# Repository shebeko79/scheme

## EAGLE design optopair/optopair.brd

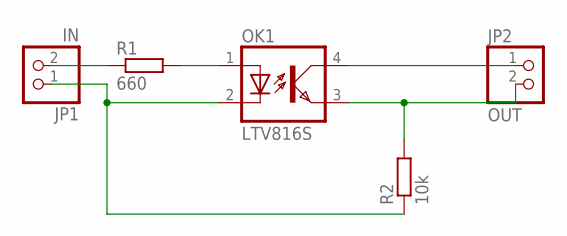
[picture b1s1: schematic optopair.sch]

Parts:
JP1: IN; 1X02
JP2: OUT; 1X02
OK1: LTV816S; SMD4
R1: 660; R0805
R2: 10k; R0805

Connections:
unnamed: JP1.2, R1.1
unnamed: OK1.1 (A), R1.2
unnamed: JP1.1, OK1.2 (C), R2.1
unnamed: JP2.2, OK1.3 (EMIT), R2.2
unnamed: JP2.1, OK1.4 (COL)

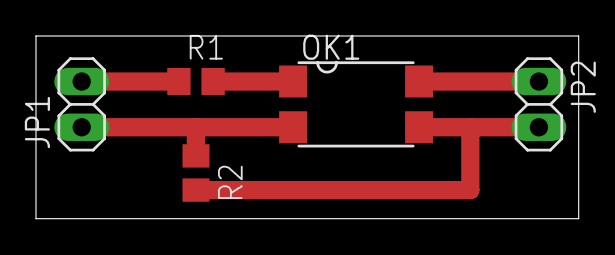
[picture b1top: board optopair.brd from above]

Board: 2 copper layers, 30.2 x 10.2 mm, 5 parts (0 on the bottom side), 5 nets.

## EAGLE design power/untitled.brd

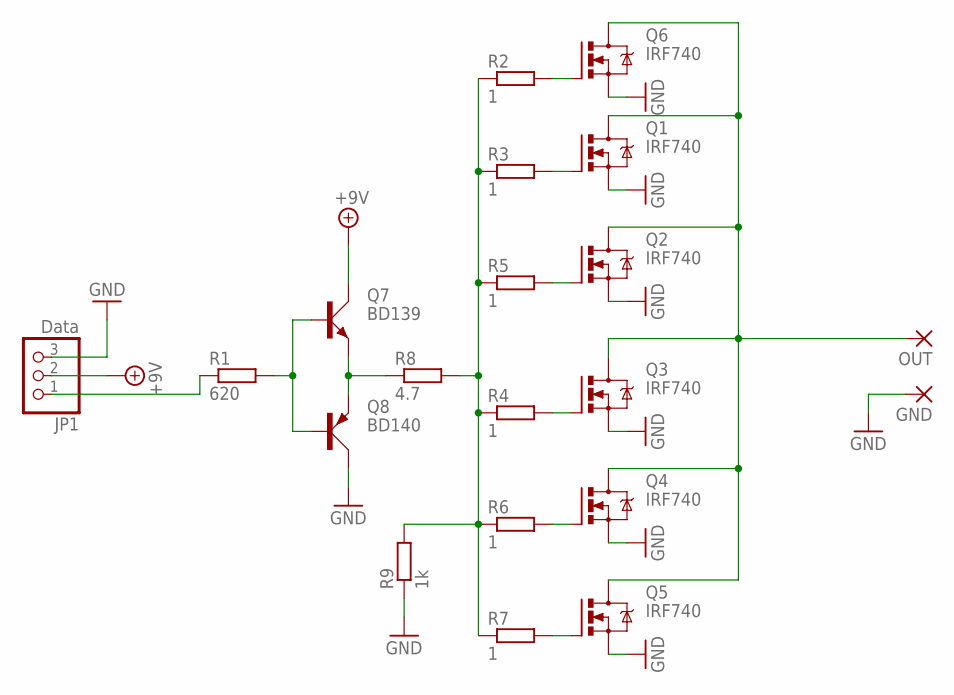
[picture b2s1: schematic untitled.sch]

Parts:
GND: WIREPADSMD5-2,5; 5-2,5
JP1: Data; 1X03
OUT: WIREPADSMD5-2,5; 5-2,5
Q1, Q2, Q3, Q4, Q5, Q6: IRF740; TO220BV
Q7: BD139; TO126AV
Q8: BD140; TO126AV
R1: 620; R0805
R2, R3, R4, R5, R6, R7: 1; R0805
R8: 4.7; R0805
R9: 1k; R0805

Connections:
+9V: JP1.2, Q7.C
GND: GND.1, JP1.3, Q1.S, Q2.S, Q3.S, Q4.S, Q5.S, Q6.S, Q8.C, R9.1
unnamed: Q7.B, Q8.B, R1.2
unnamed: OUT.1, Q1.D, Q2.D, Q3.D, Q4.D, Q5.D, Q6.D
unnamed: Q7.E, Q8.E, R8.1
unnamed: R2.1, R3.1, R4.1, R5.1, R6.1, R7.1, R8.2, R9.2
unnamed: Q6.G, R2.2
unnamed: Q1.G, R3.2
unnamed: Q2.G, R5.2
unnamed: Q3.G, R4.2
unnamed: Q4.G, R6.2
unnamed: Q5.G, R7.2
unnamed: JP1.1, R1.1

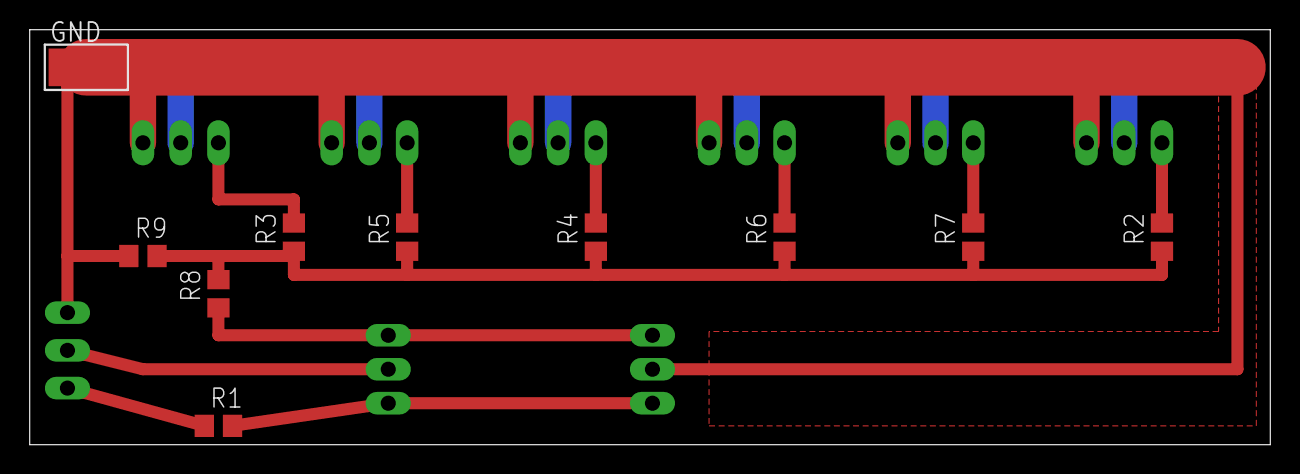
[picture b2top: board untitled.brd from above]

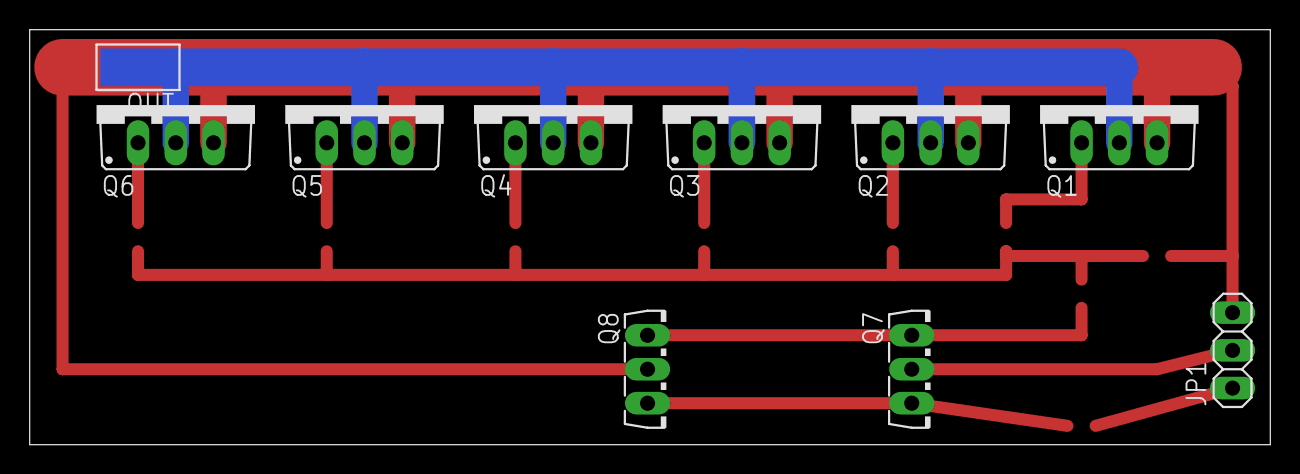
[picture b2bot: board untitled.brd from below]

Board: 2 copper layers, 83.5 x 27.9 mm, 20 parts (10 on the bottom side), 13 nets.

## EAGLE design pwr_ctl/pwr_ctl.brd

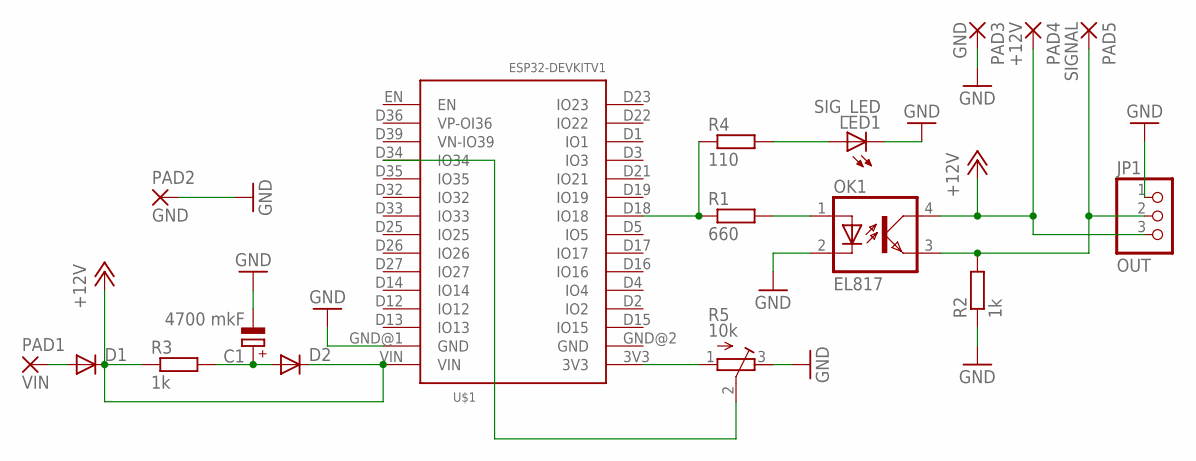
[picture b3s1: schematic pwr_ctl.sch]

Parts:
C1: 4700 mkF; E7,5-18
D1, D2: CGRM4007-G; SOD-123_MINI-SMA
JP1: OUT; 1X03
LED1: SIG_LED; SML0805
OK1: EL817; SMD4
PAD1: VIN; SMD2,54-5,08
PAD2, PAD3: GND; SMD2,54-5,08
PAD4: +12V; SMD2,54-5,08
PAD5: SIGNAL; SMD2,54-5,08
R1: 660; R0805
R2, R3: 1k; R0805
R4: 110; R0805
R5: 10k; RTRIM3296W
U$1: ESP32DEVKITV1; ESP32-DEVKITV1

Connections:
+12V: D1.C, D2.C, JP1.3, OK1.4 (COL), PAD4.1, R3.1, U$1.VIN
GND: C1.-, JP1.1, LED1.C, OK1.2 (C), PAD2.1, PAD3.1, R2.1, R5.3 (E), U$1.GND@1 (GND)
unnamed: R1.1, R4.1, U$1.D18 (IO18)
unnamed: OK1.1 (A), R1.2
unnamed: R5.1 (A), U$1.3V3
unnamed: C1.+, D2.A, R3.2
unnamed: LED1.A, R4.2
unnamed: D1.A, PAD1.1
unnamed: JP1.2, OK1.3 (EMIT), PAD5.1, R2.2
unnamed: R5.2 (S), U$1.D34 (IO34)

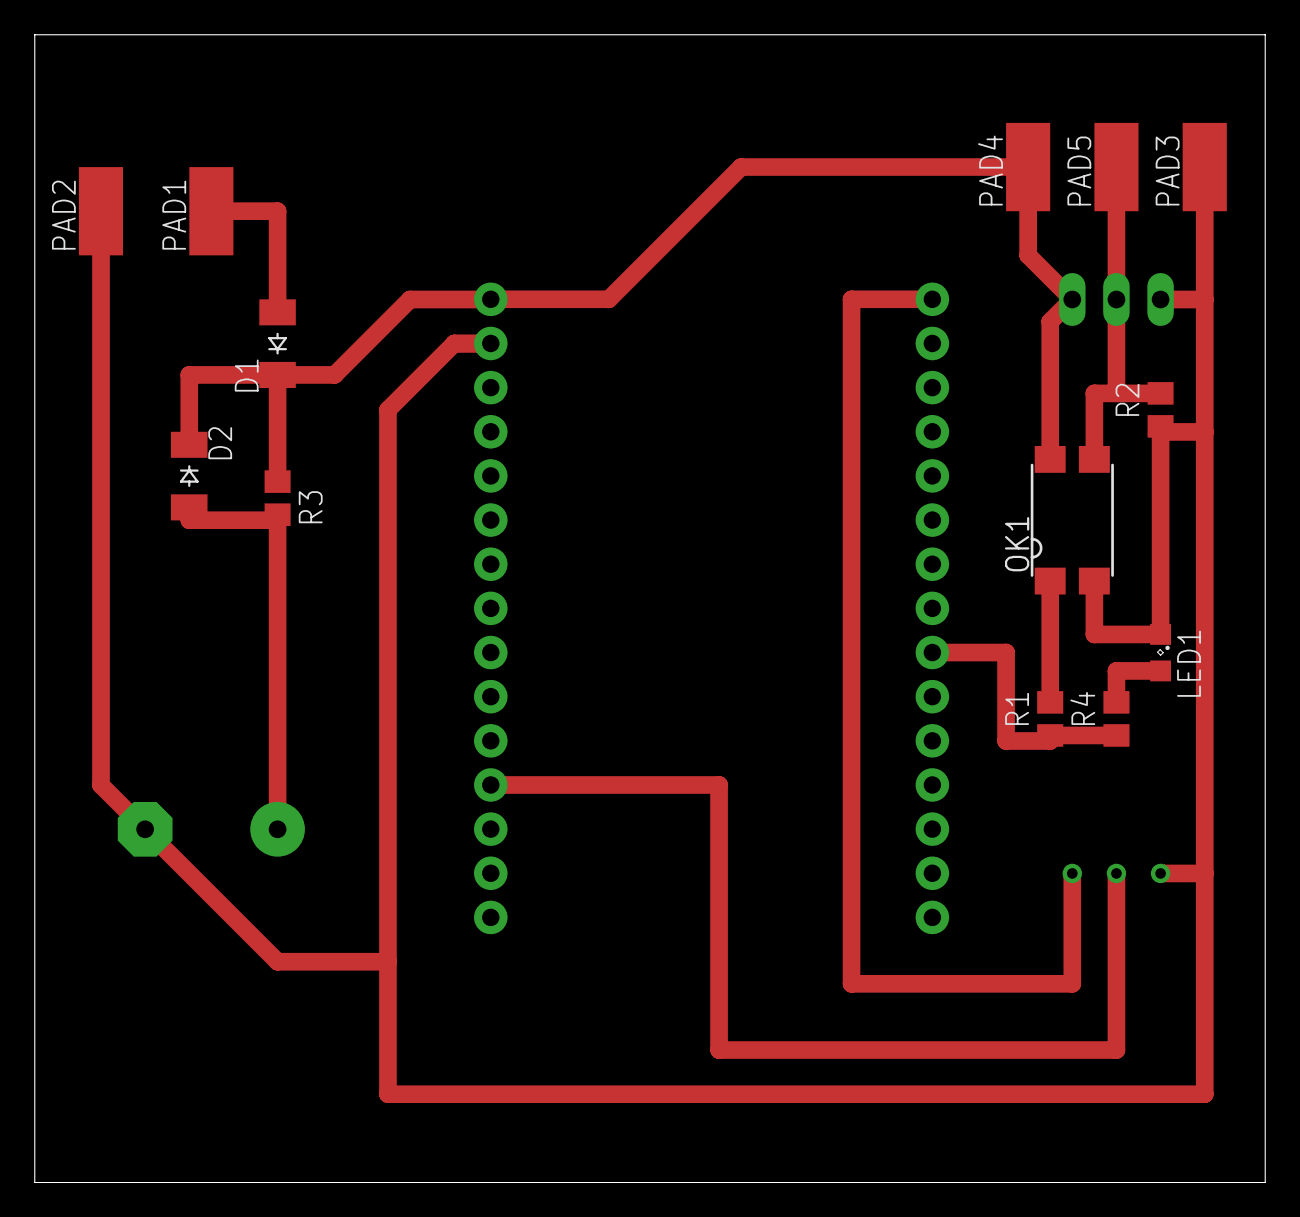
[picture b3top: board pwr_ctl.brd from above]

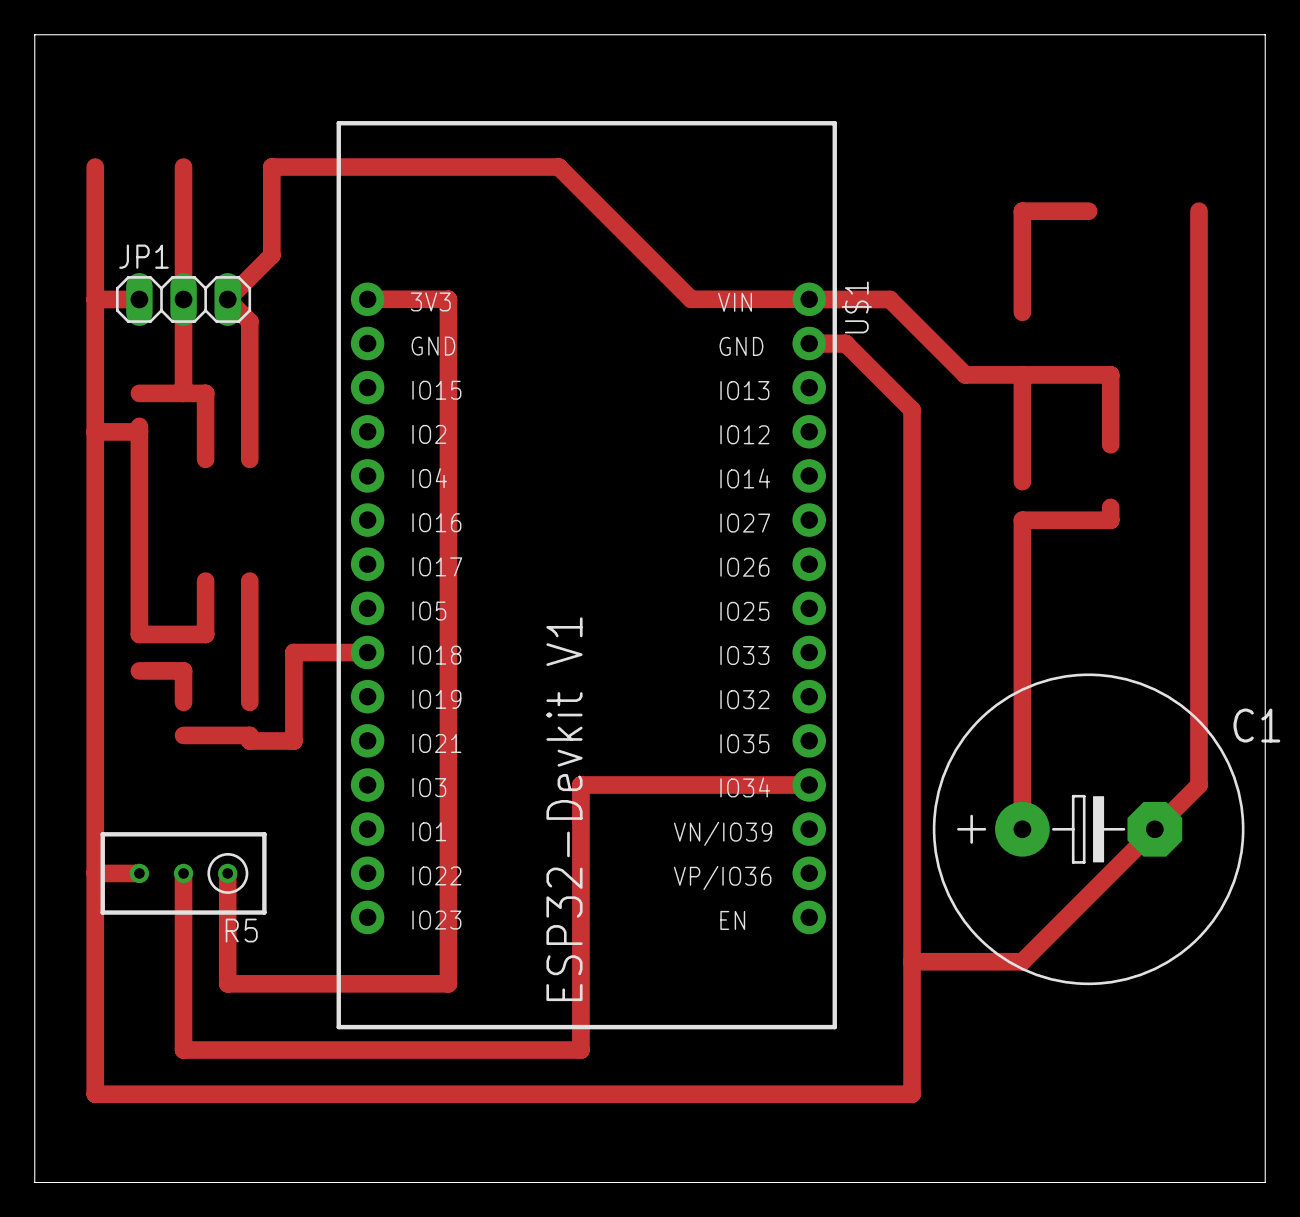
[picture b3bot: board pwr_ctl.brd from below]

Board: 2 copper layers, 70.8 x 66.0 mm, 17 parts (4 on the bottom side), 10 nets.

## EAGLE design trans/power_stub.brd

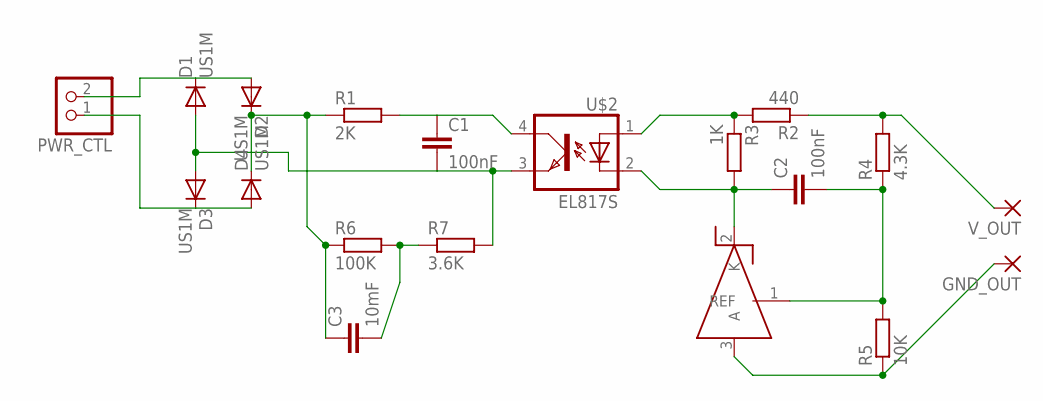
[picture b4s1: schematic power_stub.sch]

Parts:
C1, C2: 100nF; C0805
C3: 10mF; C0805
D1, D2, D3, D4: US1M; DO-214AC
GND_OUT: SMD5; SMD2,54-5,08
PWR_CTL: PINHD-1X2/90; 1X02/90
R1: 2K; R0805
R2: 440; R0805
R3: 1K; R0805
R4: 4.3K; R0805
R5: 10K; R0805
R6: 100K; R0805
R7: 3.6K; R0805
U$1: TL431AIDBZR; SOT23
U$2: EL817S; SMD4_L
V_OUT: SMD5; SMD2,54-5,08

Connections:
GND: GND_OUT.1, R5.1, U$1.3 (A)
GND_HI: C1.2, D1.A, D3.A, R7.2, U$2.3 (EMIT)
unnamed: D1.C, D2.A, PWR_CTL.2
unnamed: C1.1, R1.2, U$2.4 (COL)
unnamed: D3.C, D4.A, PWR_CTL.1
unnamed: C2.1, R3.2, U$1.2 (K), U$2.2 (C)
unnamed: R2.1, R4.2, V_OUT.1
unnamed: C2.2, R4.1, R5.2, U$1.1 (REF)
unnamed: C3.2, R6.2, R7.1
unnamed: R2.2, R3.1, U$2.1 (A)
V_HI: C3.1, D2.C, D4.C, R1.1, R6.1

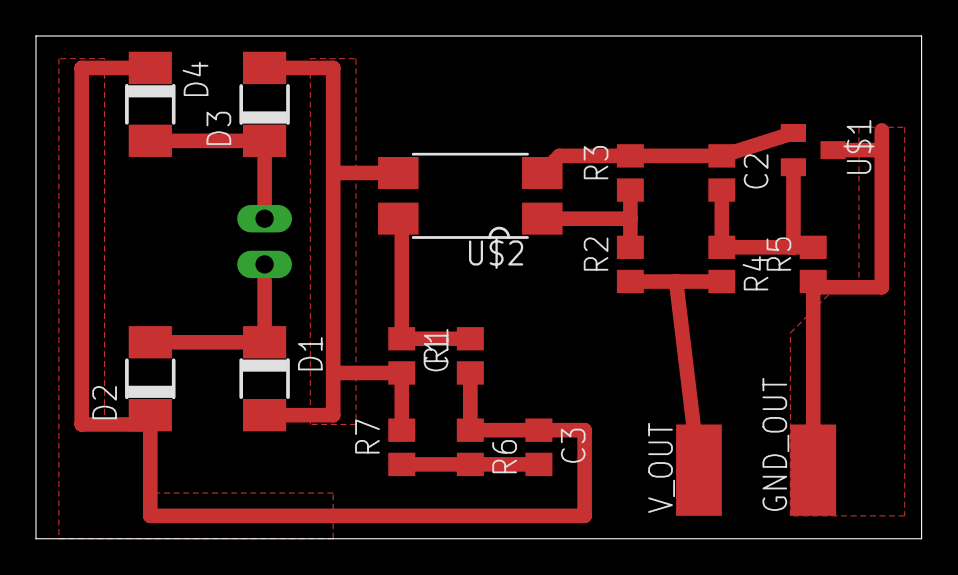
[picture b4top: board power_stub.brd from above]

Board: 2 copper layers, 49.2 x 27.9 mm, 19 parts (1 on the bottom side), 11 nets.

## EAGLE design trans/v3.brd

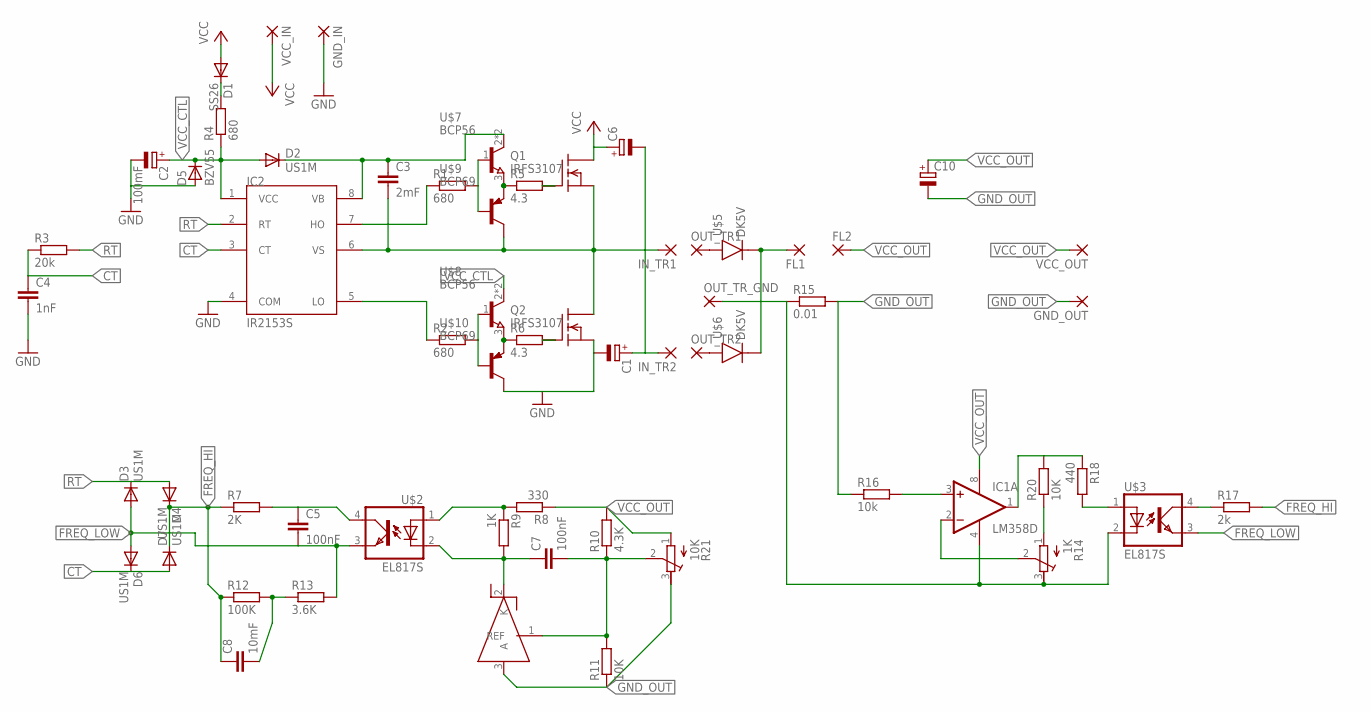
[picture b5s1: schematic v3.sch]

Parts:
C1, C6: CPOL-EUE10-22.5; EB22,5D
C2: 100mF; E5-10,5
C3: 2mF; C0805
C4: 1nF; C0805
C5, C7: 100nF; C0805
C8: 10mF; C0805
C10: CPOL-EUE7.5-18; E7,5-18
D1: SS26; DO-214AC
D2, D3, D4, D6, D7: US1M; DO-214AC
D5: BZV55; SOD80
FL1, FL2: 3,81/1,4
GND_IN: 3,81/1,4
GND_OUT: 3,81/1,4
IC1: LM358D; SO08
IC2: IR2153S; SO08
IN_TR1, IN_TR2: 3,81/1,4
OUT_TR1, OUT_TR2: 3,81/1,4
OUT_TR_GND: 3,81/1,4
Q1, Q2: IRFS3107; D2PAK
R1, R2, R4: 680; R0805
R3: 20k; R0805
R5, R6: 4.3; R0805
R7: 2K; R0805
R8: 330; R0805
R9: 1K; R0805
R10: 4.3K; R0805
R11: 10K; R0805
R12: 100K; R0805
R13: 3.6K; R0805
R14: 1K; RTRIM3296W
R15: 0.01; R2512
R16: 10k; M0805
R17: 2k; M0805
R18: 440; M0805
R20: 10K; M0805
R21: 10K; RTRIM3296W
U$1: TL431; SOT23
U$2, U$3: EL817S; SMD4_L
U$5, U$6: DK5V; TO220(V)
U$7, U$8: BCP56; SOT223
U$9, U$10: BCP69; SOT223
VCC_IN: 3,81/1,4
VCC_OUT: 3,81/1,4

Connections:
CT: C4.1, D6.C, D7.A, IC2.3 (CT), R3.1
FREQ_HI: C8.1, D4.C, D7.C, R7.1, R12.1, R17.2
FREQ_LOW: C5.2, D3.A, D6.A, R13.2, U$2.3 (EMIT), U$3.3 (EMIT)
GND: C1.-, C2.-, C4.2, D5.2 (A), GND_IN.1, IC2.4 (COM), Q2.3 (S), U$10.2 (C), U$10.4 (C)
GND_OUT: C10.-, GND_OUT.1, R11.1, R15.2, R16.1, R21.3 (E), U$1.3 (A)
IN_TR1: C3.2, IC2.6 (VS), IN_TR1.1, Q1.3 (S), Q2.2 (D), U$9.2 (C), U$9.4 (C)
IN_TR2: C1.+, C6.-, IN_TR2.1
unnamed: R1.2, U$7.1 (B), U$9.1 (B)
unnamed: R2.2, U$8.1 (B), U$10.1 (B)
unnamed: OUT_TR1.1, U$5.IN (A)
unnamed: R5.1, U$7.3 (E), U$9.3 (E)
unnamed: R6.1, U$8.3 (E), U$10.3 (E)
unnamed: Q1.1 (G), R5.2
unnamed: OUT_TR2.1, U$6.IN (A)
unnamed: C5.1, R7.2, U$2.4 (COL)
unnamed: Q2.1 (G), R6.2
unnamed: IC2.7 (HO), R1.1
unnamed: IC2.5 (LO), R2.1
unnamed: D1.C, R4.2
unnamed: C7.1, R9.2, U$1.2 (K), U$2.2 (C)
unnamed: C7.2, R10.1, R11.2, R21.2 (S), U$1.1 (REF)
unnamed: R8.2, R9.1, U$2.1 (A)
unnamed: C8.2, R12.2, R13.1
unnamed: R18.2, U$3.1 (A)
unnamed: IC1.3 (+IN), R16.2
unnamed: IC1.4 (V-), OUT_TR_GND.1, R14.3 (E), R15.1, U$3.2 (C)
unnamed: IC1.1 (OUT), R18.1, R20.2
unnamed: IC1.2 (-IN), R14.2 (S)
unnamed: R14.1 (A), R20.1
unnamed: R17.1, U$3.4 (COL)
RT: D3.C, D4.A, IC2.2 (RT), R3.2
VB: C3.1, D2.C, IC2.8 (VB), U$7.2 (C), U$7.4 (C)
VCC: C6.+, D1.A, Q1.2 (D), VCC_IN.1
VCC_CTL: C2.+, D2.A, D5.1 (C), IC2.1 (VCC), R4.1, U$8.2 (C), U$8.4 (C)
VCC_OUT: C10.+, FL2.1, IC1.8 (V+), R8.1, R10.2, R21.1 (A), VCC_OUT.1
VCC_RECTIFIER: FL1.1, U$5.GND (K), U$6.GND (K)

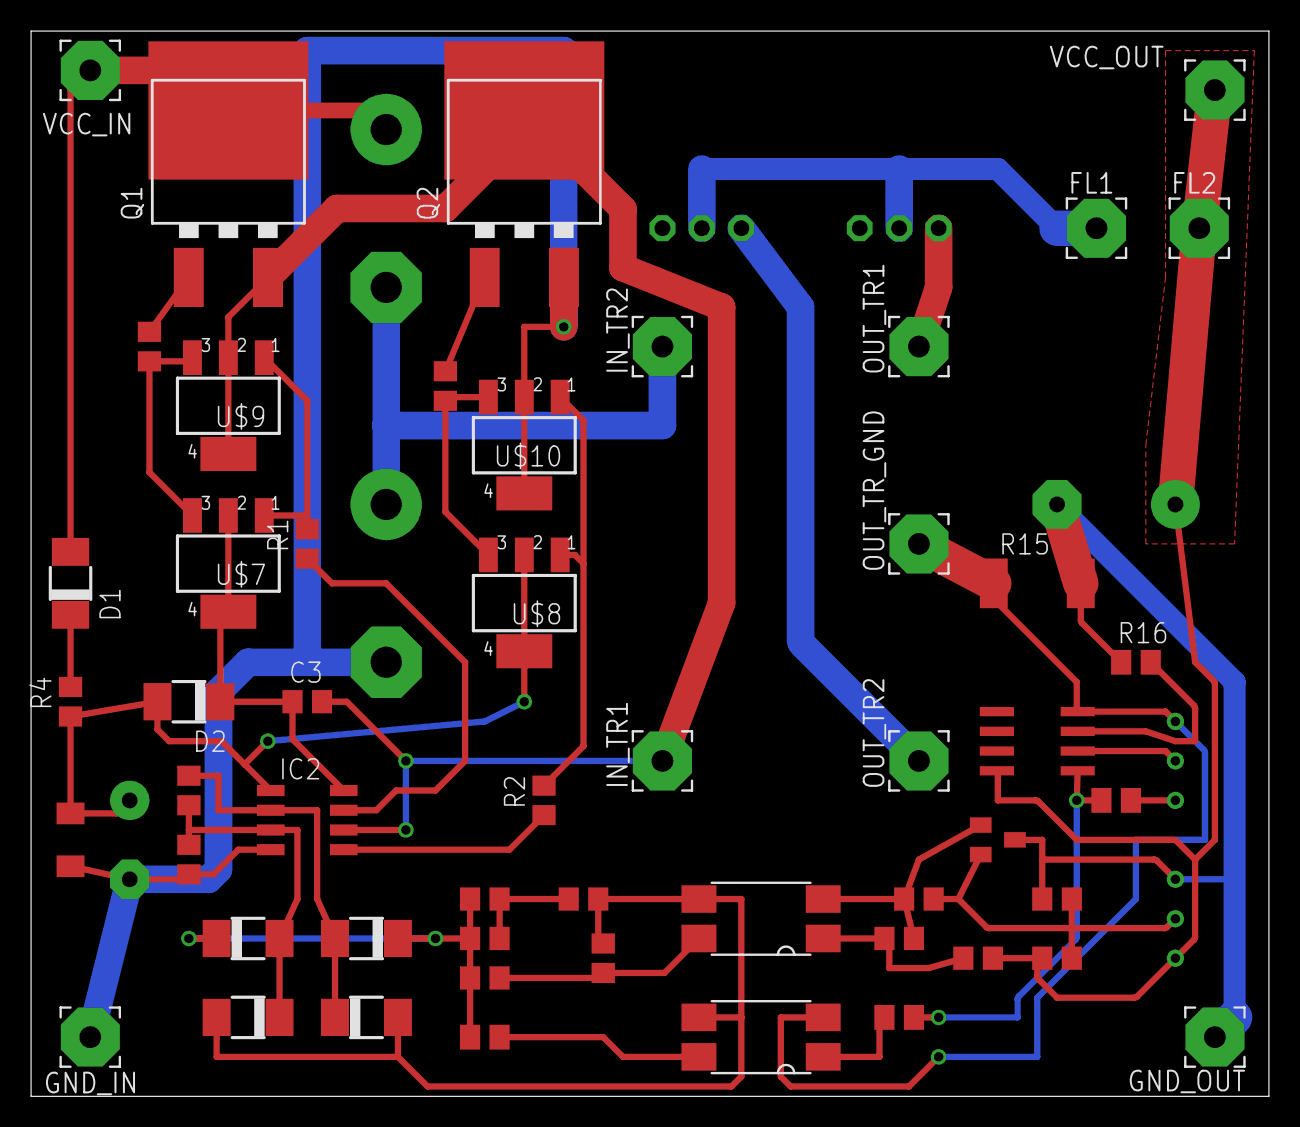
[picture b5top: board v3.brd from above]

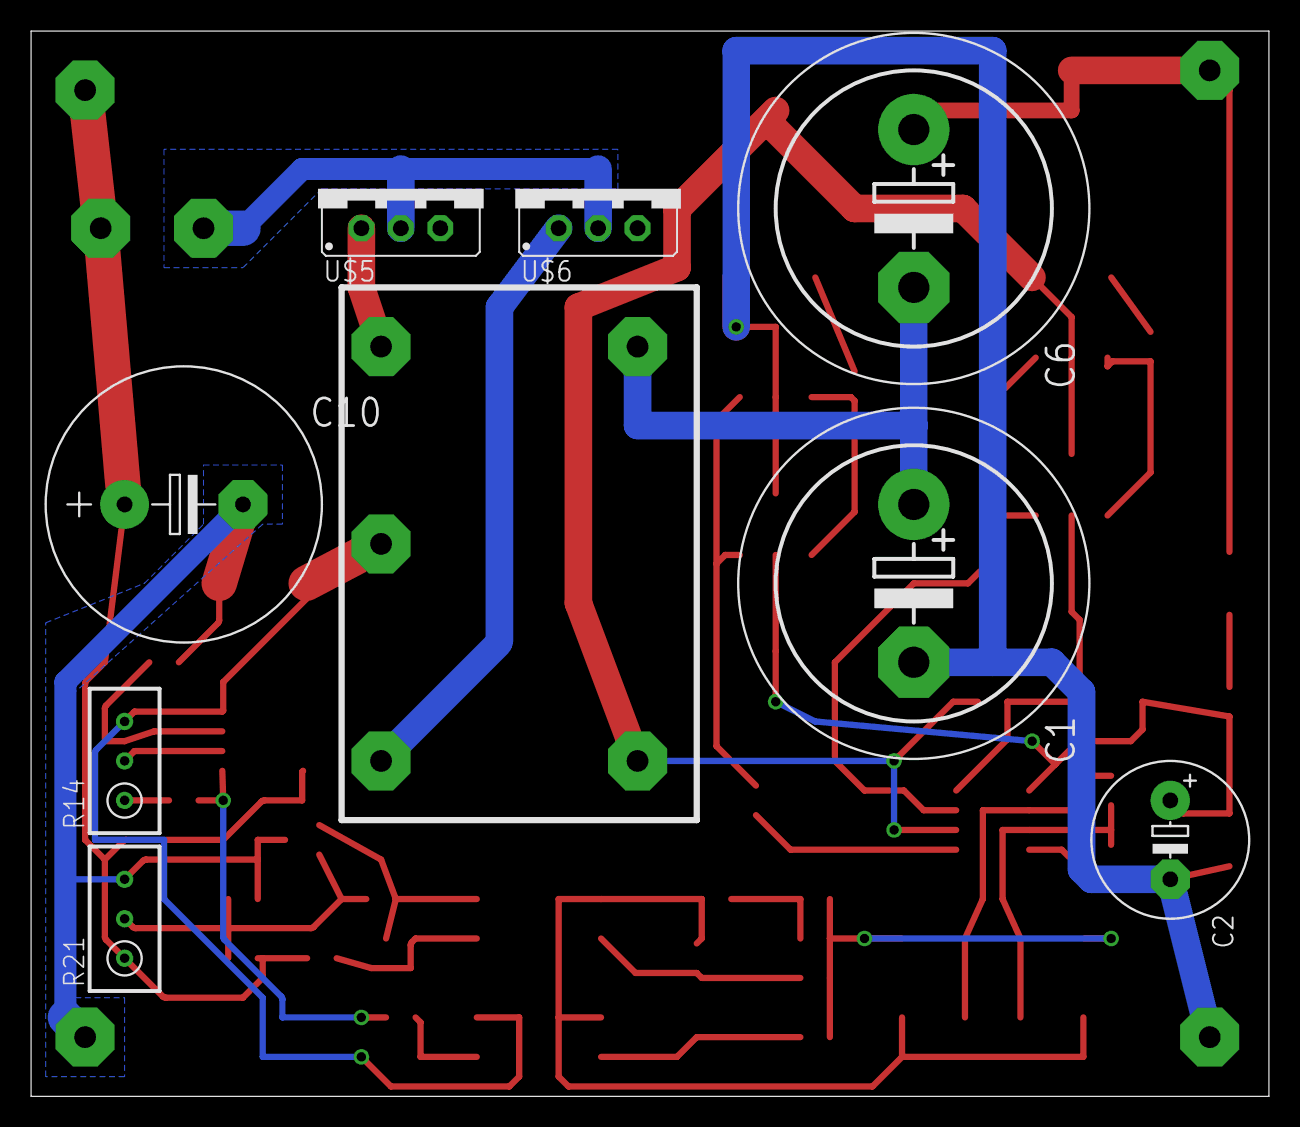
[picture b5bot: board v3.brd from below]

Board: 2 copper layers, 79.7 x 68.6 mm, 60 parts (8 on the bottom side), 36 nets.
